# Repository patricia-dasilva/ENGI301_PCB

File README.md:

# ENGI301_PCB
Location for all files used to complete PCB design projects in ENGI301

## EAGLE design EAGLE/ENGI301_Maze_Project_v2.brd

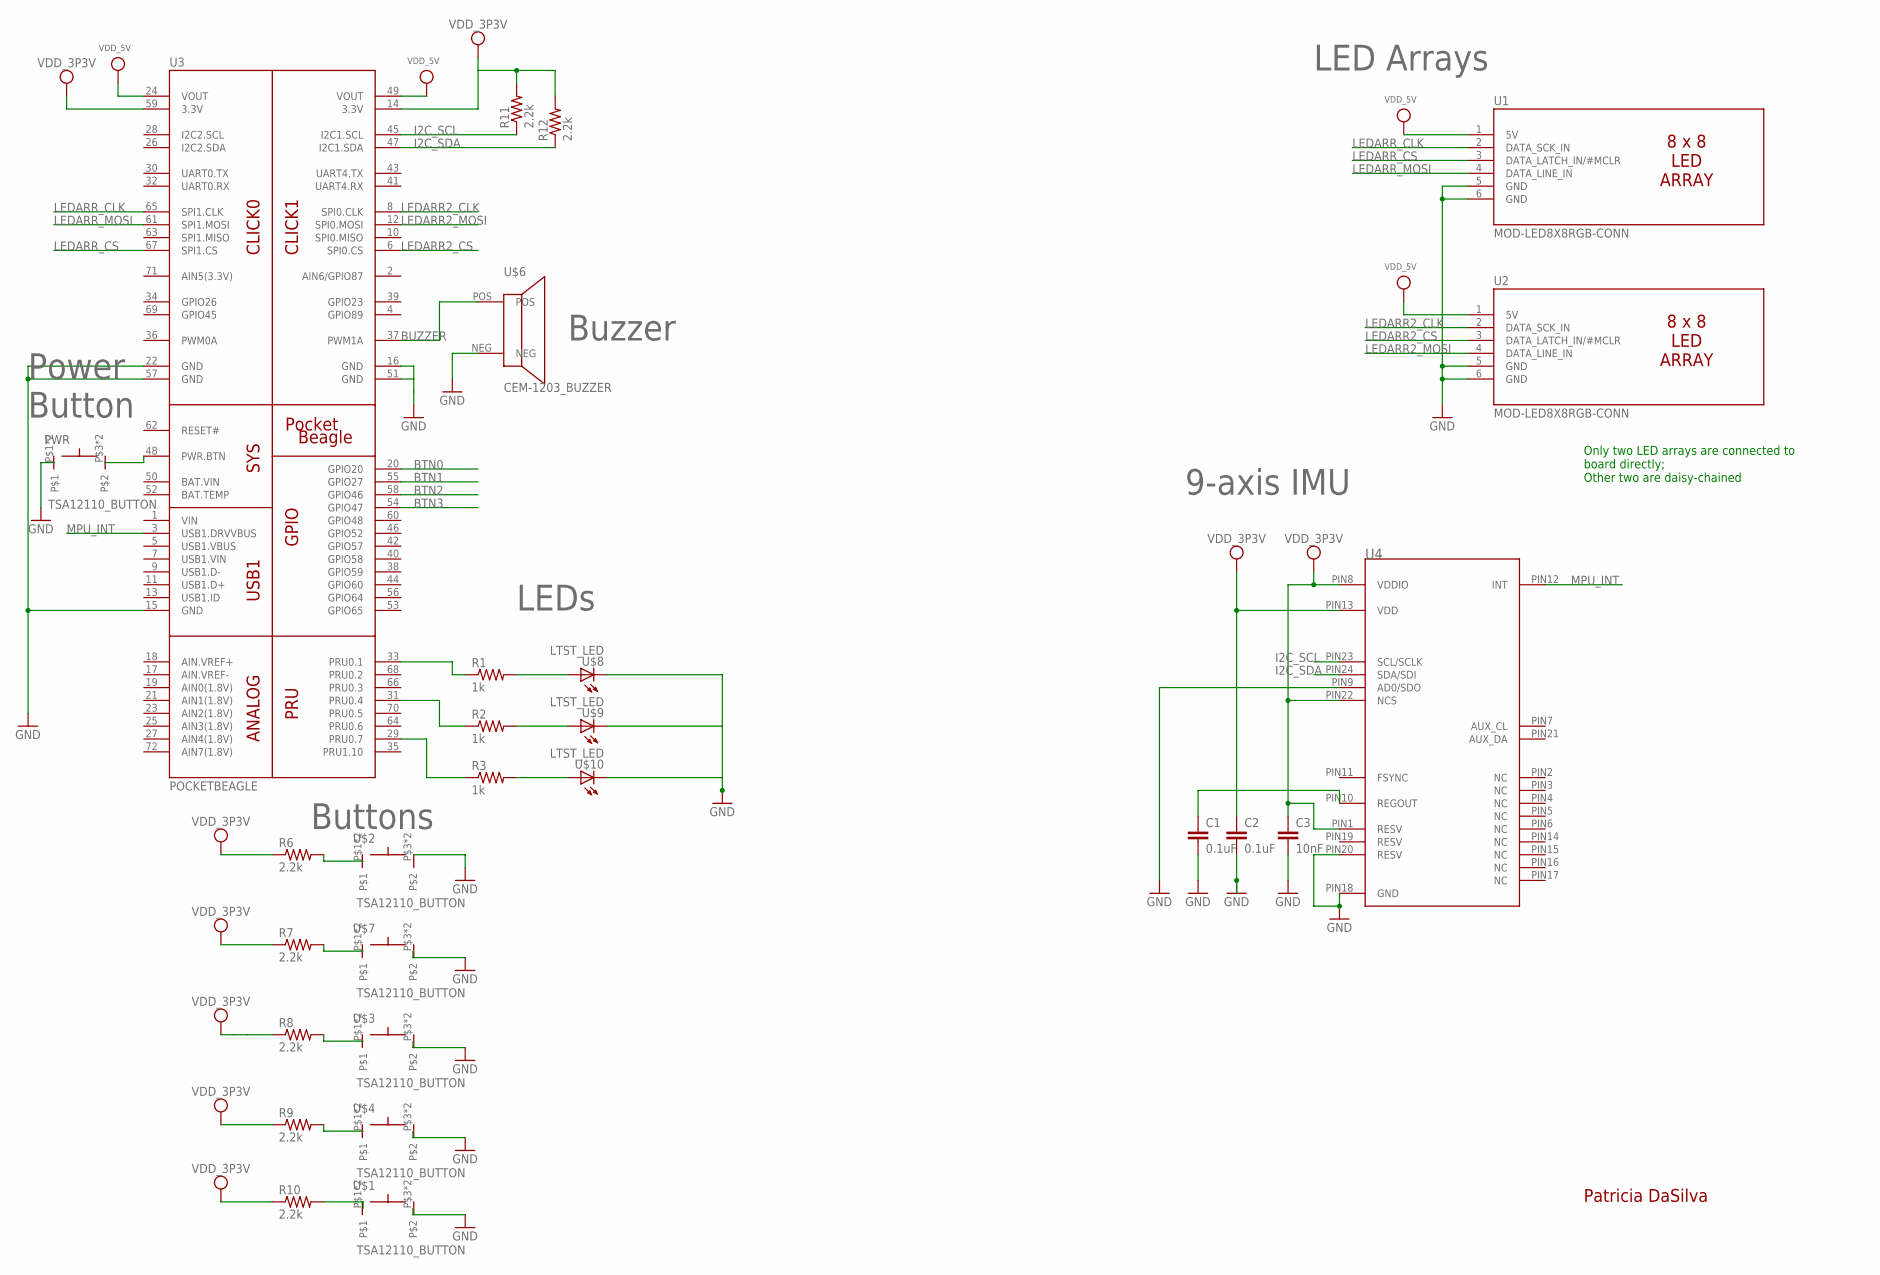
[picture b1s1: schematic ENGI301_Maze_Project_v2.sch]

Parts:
C1, C2: 0.1uF; C0402
C3: 10nF; C0402
PWR: TSA12110_BUTTON; 4HOLE-THRU
R1, R2, R3: 1k; R0603
R6, R7, R8, R9, R10, R11, R12: 2.2k; R0603
U1, U2: MOD-LED8X8RGB-CONN; FE06W
U3: POCKETBEAGLE
U4: IMU_MPU9250; IMU_QFN_3MMX3MM
U$1, U$2, U$3, U$4, U$7: TSA12110_BUTTON; 4HOLE-THRU
U$6: CEM-1203_BUZZER; 2HOLE-THRU
U$8, U$9, U$10: LTST_LED; SMD_0.8X0.8MM

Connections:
BTN0: U3.20 (GPIO20)
BTN1: U3.55 (GPIO27)
BTN2: U3.58 (GPIO46)
BTN3: U3.54 (GPIO47)
BUZZER: U3.37 (PWM1A), U$6.POS
GND: C1.2, C2.2, C3.2, PWR.P$1, PWR.P$2, U1.5 (GND), U1.6 (GND), U2.5 (GND), U2.6 (GND), U3.15 (GND), U3.16 (GND), U3.22 (GND), U3.51 (GND), U3.57 (GND), U4.PIN9 (AD0/SDO), U4.PIN18 (GND), U4.PIN20 (RESV), U$1.P$3, U$1.P$4, U$3.P$3, U$3.P$4, U$4.P$3, U$4.P$4, U$6.NEG, U$7.P$3, U$7.P$4, U$8.C (CATHODE), U$9.C (CATHODE), U$10.C (CATHODE)
I2C_SCL: R11.1, U3.45 (I2C1.SCL), U4.PIN23 (SCL/SCLK)
I2C_SDA: R12.1, U3.47 (I2C1.SDA), U4.PIN24 (SDA/SDI)
LEDARR2_CLK: U2.2 (DATA_SCK_IN), U3.8 (SPI0.CLK)
LEDARR2_CS: U2.3 (DATA_LATCH_IN/#MCLR), U3.6 (SPI0.CS)
LEDARR2_MOSI: U2.4 (DATA_LINE_IN), U3.12 (SPI0.MOSI)
LEDARR_CLK: U1.2 (DATA_SCK_IN), U3.65 (SPI1.CLK)
LEDARR_CS: U1.3 (DATA_LATCH_IN/#MCLR), U3.67 (SPI1.CS)
LEDARR_MOSI: U1.4 (DATA_LINE_IN), U3.61 (SPI1.MOSI)
MPU_INT: U3.3 (USB1.DRVVBUS), U4.PIN12 (INT)
unnamed: PWR.P$3, PWR.P$4, U3.48 (PWR.BTN)
unnamed: R1.1, U3.33 (PRU0.1)
unnamed: R2.1, U3.31 (PRU0.4)
unnamed: C1.1, U4.PIN10 (REGOUT)
unnamed: R3.1, U3.29 (PRU0.7)
unnamed: R6.2, U$2.P$1, U$2.P$2
unnamed: R1.2, U$8.A (ANODE)
unnamed: R7.2, U$7.P$1, U$7.P$2
unnamed: R2.2, U$9.A (ANODE)
unnamed: R8.2, U$3.P$1, U$3.P$2
unnamed: R3.2, U$10.A (ANODE)
unnamed: R9.2, U$4.P$1, U$4.P$2
unnamed: R10.2, U$1.P$1, U$1.P$2
SYS_VDD1_3P3V: C2.1, C3.1, R6.1, R7.1, R8.1, R9.1, R10.1, R11.2, R12.2, U3.14 (3.3V), U3.59 (3.3V), U4.PIN1 (RESV), U4.PIN8 (VDDIO), U4.PIN13 (VDD), U4.PIN22 (NCS)
SYS_VDD1_5V: U1.1 (5V), U2.1 (5V), U3.24 (VOUT), U3.49 (VOUT)

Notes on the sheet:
Patricia DaSilva
9-axis IMU
LED Arrays
Buttons
LEDs
Power Button
Buzzer
Only two LED arrays are connected to board directly; Other two are daisy-chained

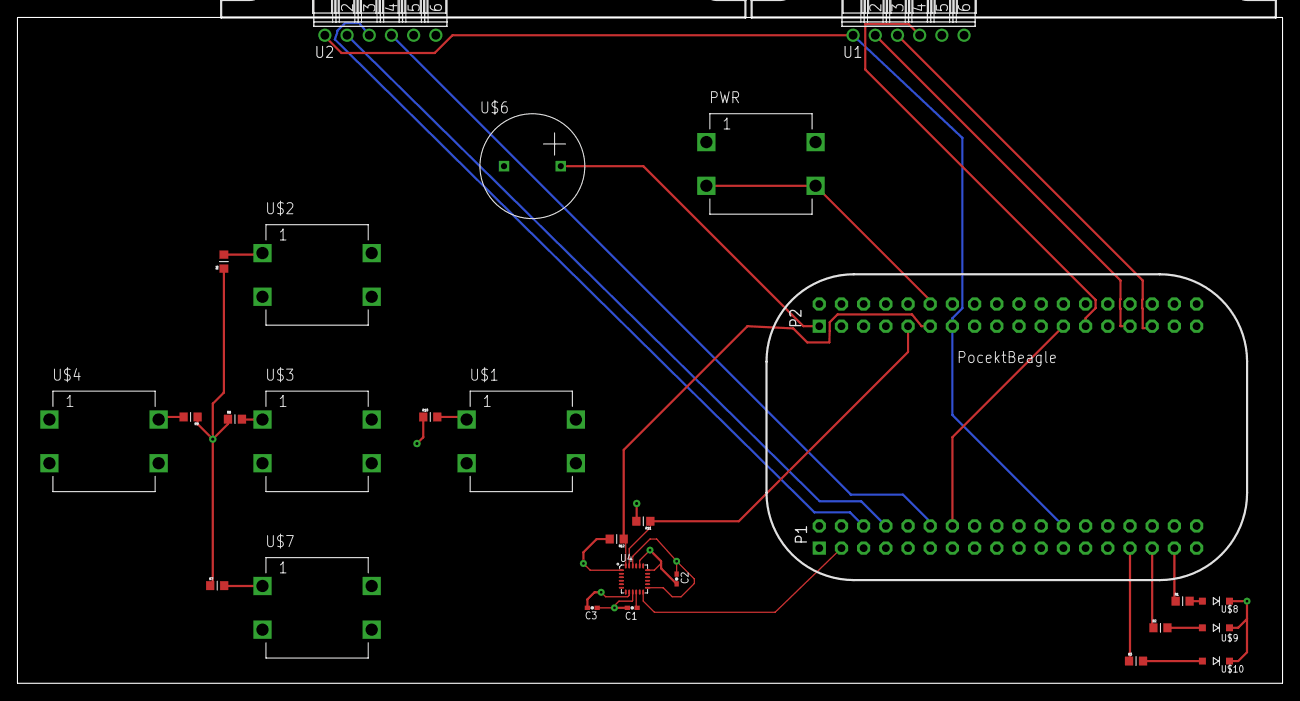
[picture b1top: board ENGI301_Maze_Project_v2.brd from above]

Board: 4 copper layers, 144.8 x 76.2 mm, 29 parts (0 on the bottom side), 26 nets.

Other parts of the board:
U$5, U$11: MOD-LED8X8RGB

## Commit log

2018-04-09 library files for LED, button, and buzzer.
2018-04-20 Final library, schematic and board.
2018-04-21 Gerber files for maze project board.
2018-04-23 Added pictures of top and bottom layer.
